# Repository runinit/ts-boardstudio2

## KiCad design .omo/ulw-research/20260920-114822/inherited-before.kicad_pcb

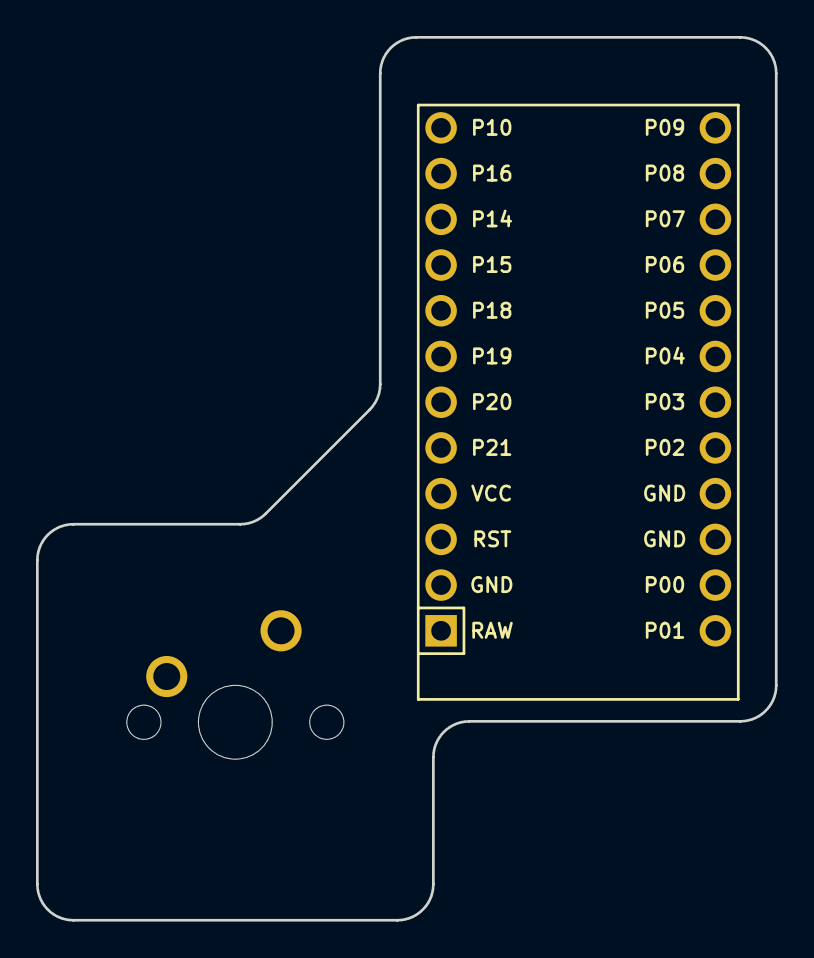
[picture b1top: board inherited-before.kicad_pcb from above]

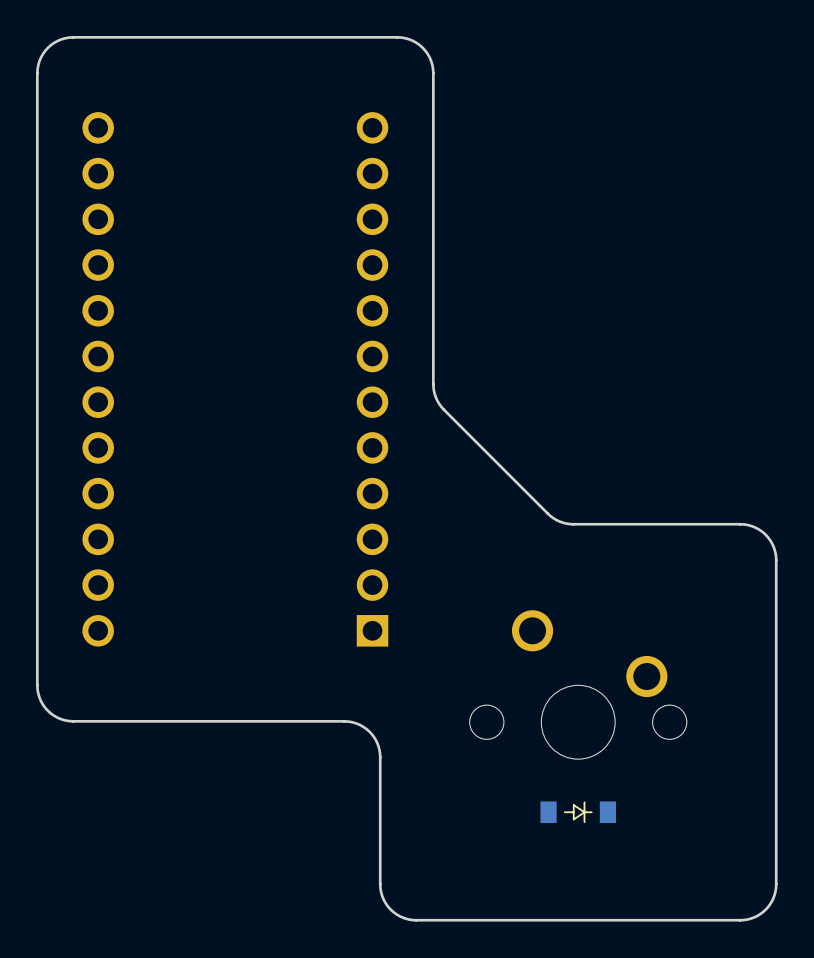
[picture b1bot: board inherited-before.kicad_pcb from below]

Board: 2 copper layers, 41.0 x 49.0 mm, 3 parts (2 on the bottom side), 3 nets, no tracks yet.

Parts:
X16970d43: ProMicro
Xec10466e: diode_tht_sod123
Xf89d51b7: switch_mx

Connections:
GND: X16970d43.2, X16970d43.15, X16970d43.16
R1: X16970d43.13, Xec10466e.1
fingers_c1_r1_switch: Xec10466e.2, Xf89d51b7.2

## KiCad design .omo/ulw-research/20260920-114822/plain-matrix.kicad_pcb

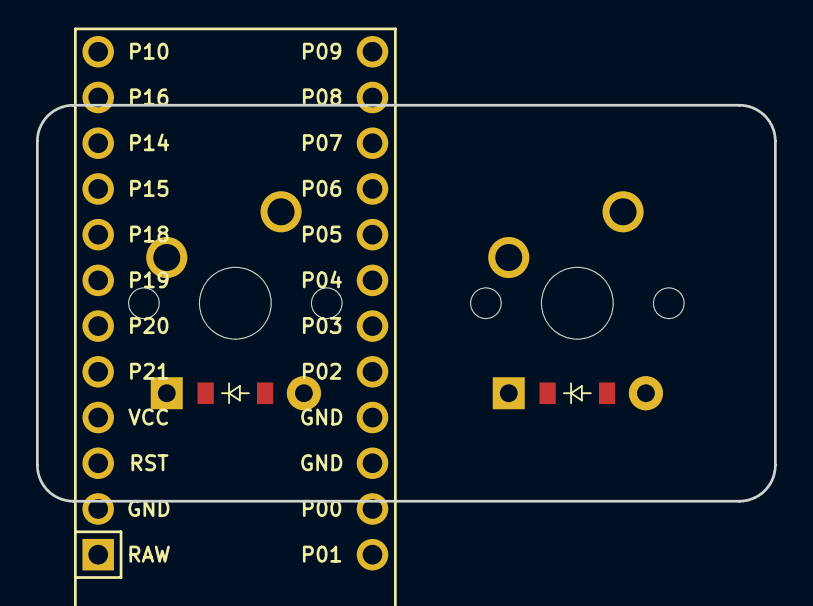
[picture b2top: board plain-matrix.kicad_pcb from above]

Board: 2 copper layers, 41.0 x 22.0 mm, 5 parts (0 on the bottom side), 4 nets, no tracks yet.

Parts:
X8d4cc759: ComboDiode
X9c733b1c: ProMicro
X876ba2fe: MX
Xb2d7db84: ComboDiode
Xf89d51b7: MX

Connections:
GND: X9c733b1c.2, X9c733b1c.15, X9c733b1c.16
fingers_c1_r1_switch: X8d4cc759.2, Xf89d51b7.2
fingers_c2_r1_switch: X876ba2fe.2, Xb2d7db84.2
fingers_r1: X8d4cc759.1, Xb2d7db84.1
